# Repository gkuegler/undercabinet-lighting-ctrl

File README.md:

<!-- | Supported Targets | ESP32 | ESP32-C2 | ESP32-C3 | ESP32-C6 | ESP32-H2 | ESP32-P4 | ESP32-S2 | ESP32-S3 | -->
<!-- | ----------------- | ----- | -------- | -------- | -------- | -------- | -------- | -------- | -------- | -->
| Supported Targets: | ESP32 | ESP32-S3 |
| ------------ | --- | --- |

Uses ESP-IDF v5.2

# Kitchen Under Cabinet Lighting Controller
This controller mounts upside down underneath kitchen cabinets enables the undercabinet lighting to be turned on/off with with wave of a hand.
This is the source code for a gesture activated lighting controller which utilizes a HC-SR04 ultrasonic distance sensor.

This controller is designed to be mounted upside down underneath kitchen cabinets. It's compatible with 12-24VDC LEDs.

# 3D Printed Case
The custom case was designed in OnShape. See the link below for the project file.
https://cad.onshape.com/documents/ef51b7b650ada663375a7fe6/w/94d192bce853b8bb4785d228/e/2ec3751c0459ca22265b7e29

## Folder contents

ESP-IDF projects are built using CMake. 

Below is short explanation of remaining files in the project folder.
```
├── CMakeLists.txt
├── components (project libraries, see ESP-IDF for info on components)
├── kicad (project files for custom PCB)
├── main
│   ├── CMakeLists.txt
│   └── main.cpp (entry point)
└── README.md
```

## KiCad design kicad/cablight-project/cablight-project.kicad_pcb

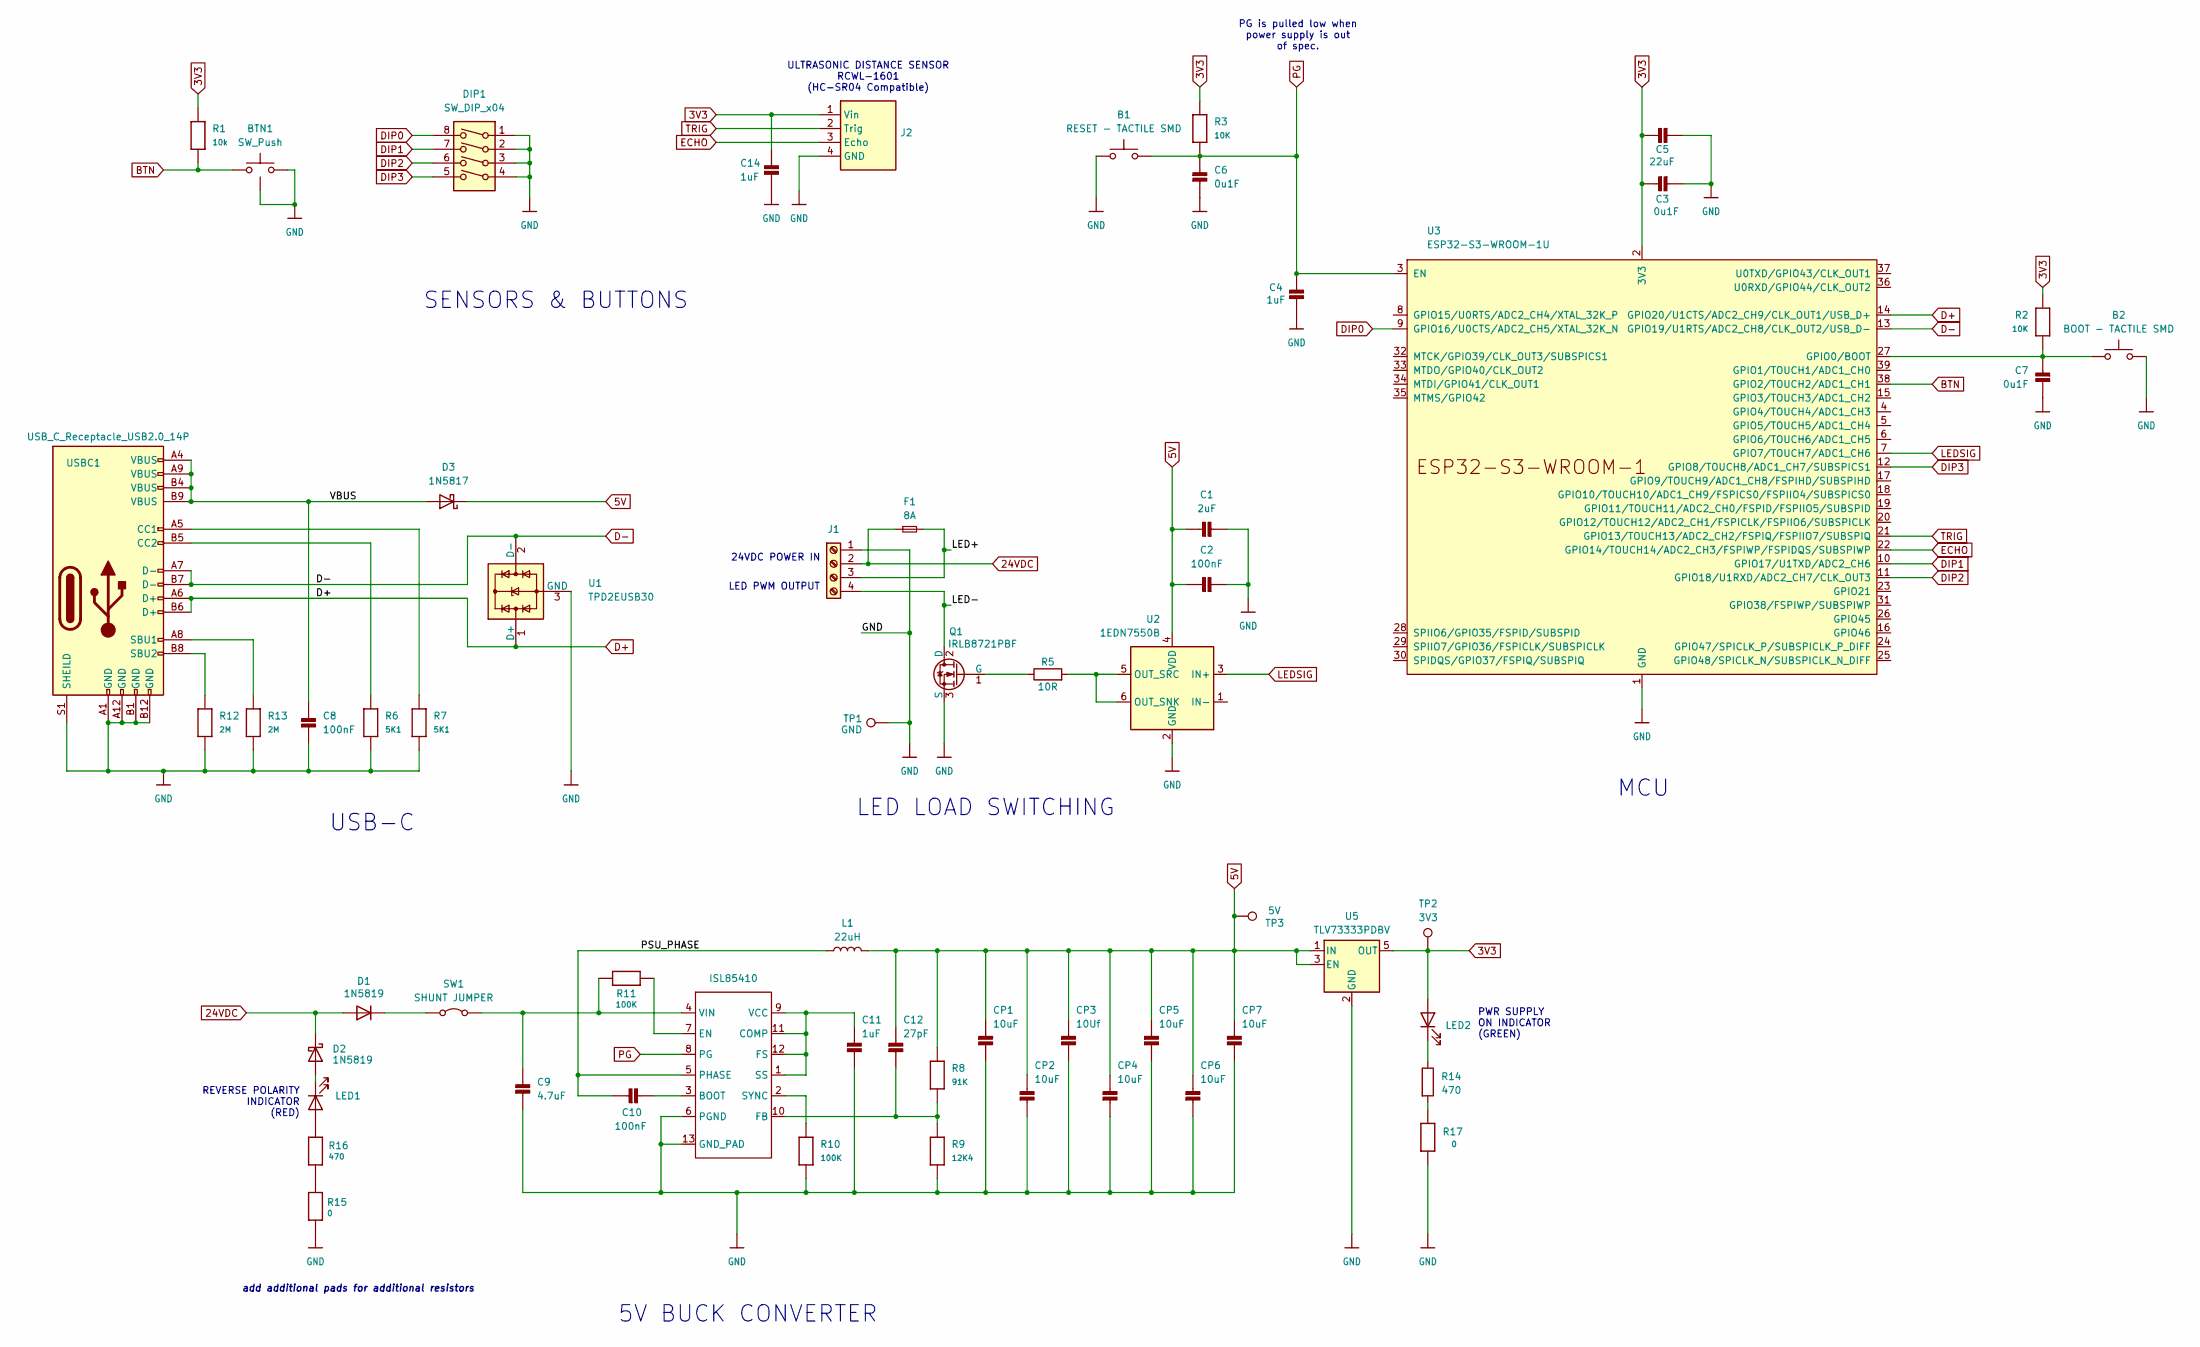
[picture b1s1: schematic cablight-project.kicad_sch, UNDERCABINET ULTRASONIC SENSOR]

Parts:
B1: RESET - TACTILE SMD; tactile Eswitch TL3365
B2: BOOT - TACTILE SMD; tactile Eswitch TL3365
BTN1: SW_Push; Tactile Switch Wurth
C1: 2uF; C_0805_2012Metric_Pad1.18x1.45mm_HandSolder
C2, C8, C10: 100nF; C_0805_2012Metric_Pad1.18x1.45mm_HandSolder
C3, C6, C7: 0u1F; C_0805_2012Metric_Pad1.18x1.45mm_HandSolder
C4, C11, C14: 1uF; C_0805_2012Metric_Pad1.18x1.45mm_HandSolder
C5: 22uF; C_0805_2012Metric_Pad1.18x1.45mm_HandSolder
C9: 4.7uF; C_0805_2012Metric_Pad1.18x1.45mm_HandSolder
C12: 27pF; C_0805_2012Metric_Pad1.18x1.45mm_HandSolder
CP1, CP2, CP4, CP5, CP6, CP7: 10uF; C_0805_2012Metric_Pad1.18x1.45mm_HandSolder
CP3: 10Uf; C_0805_2012Metric_Pad1.18x1.45mm_HandSolder
D1, D2: 1N5819; D_DO-41_SOD81_P2.54mm_Vertical_KathodeUp
D3: 1N5817; D_DO-41_SOD81_P2.54mm_Vertical_KathodeUp
DIP1: SW_DIP_x04; DIP-4 DS04-254 SAME SKY
F1: 8A; Fuse_1206_3216Metric_Pad1.42x1.75mm_HandSolder
J1: Screw_Term_1x4_5mm; Molex 4pin Terminal Block
J2: RCWL-1601; Terminal Block 4-Pin 2mm Pitch
L1: 22uH; Wurth Inductor 22uH 1.15A 225mOhm
LED1, LED2: LED 0603; LED_0603_1608Metric_Pad1.05x0.95mm_HandSolder
Q1: IRLB8721PBF; TO-220F-3_H_Heatsink
R1: 10k; R_0805_2012Metric_Pad1.20x1.40mm_HandSolder
R2, R3: 10K; R_0805_2012Metric_Pad1.20x1.40mm_HandSolder
R5: 10R; R_0805_2012Metric_Pad1.20x1.40mm_HandSolder
R6, R7: 5K1; R_0805_2012Metric_Pad1.20x1.40mm_HandSolder
R8: 91K; R_0805_2012Metric_Pad1.20x1.40mm_HandSolder
R9: 12K4; R_0805_2012Metric_Pad1.20x1.40mm_HandSolder
R10, R11: 100K; R_0805_2012Metric_Pad1.20x1.40mm_HandSolder
R12, R13: 2M; R_0805_2012Metric_Pad1.20x1.40mm_HandSolder
R14, R16: 470; R_0805_2012Metric_Pad1.20x1.40mm_HandSolder
R15, R17: 0; R_0805_2012Metric_Pad1.20x1.40mm_HandSolder
SW1: SHUNT JUMPER; 1x02_P2.54mm_Vertical_Shunt
T1: ISL85410
TP1: GND; TestPoint_THTPad_D1.0mm_Drill0.5mm
TP2: 3V3; TestPoint_THTPad_D1.0mm_Drill0.5mm
TP3: 5V; TestPoint_THTPad_D1.0mm_Drill0.5mm
U1: TPD2EUSB30; DRT3
U2: 1EDN7550B; SOT-23-6
U3: ESP32-S3-WROOM-1U
U5: TLV73333PDBV; SOT-23-5
USBC1: USB_C_Receptacle_USB2.0_14P; usbc-GCT_USB4160-03-0170-C_REVA2

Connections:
3V3: C3.1, C5.1, C14.1, J2.1 (Vin), LED2.2 (A), R1.2, R2.2, R3.2, TP2.1, U3.2 (3V3), U5.5 (OUT)
5V: C1.1, C2.1, C12.1, CP1.1, CP2.1, CP3.1, CP4.1, CP5.1, CP6.1, CP7.1, D3.1 (K), L1.2, R8.2, TP3.1, U2.4 (VDD), U5.1 (IN), U5.3 (EN)
24VDC: D1.2 (A), D2.1 (K), F1.1, J1.2
/LED+: F1.2, J1.3
/LED-: J1.4, Q1.2 (D)
/PSU_PHASE: C10.1, L1.1, T1.5 (PHASE)
/VBUS: C8.1, D3.2 (A), USBC1.A4 (VBUS), USBC1.A9 (VBUS), USBC1.B4 (VBUS), USBC1.B9 (VBUS)
BTN: BTN1.1, R1.1, U3.38 (GPIO2/TOUCH2/ADC1_CH1)
D+: U1.1 (D+), U3.14 (GPIO20/U1CTS/ADC2_CH9/CLK_OUT1/USB_D+), USBC1.A6 (D+), USBC1.B6 (D+)
D-: U1.2 (D-), U3.13 (GPIO19/U1RTS/ADC2_CH8/CLK_OUT2/USB_D-), USBC1.A7 (D-), USBC1.B7 (D-)
DIP0: DIP1.8, U3.9 (GPIO16/U0CTS/ADC2_CH5/XTAL_32K_N)
DIP1: DIP1.7, U3.10 (GPIO17/U1TXD/ADC2_CH6)
DIP2: DIP1.6, U3.11 (GPIO18/U1RXD/ADC2_CH7/CLK_OUT3)
DIP3: DIP1.5, U3.12 (GPIO8/TOUCH8/ADC1_CH7/SUBSPICS1)
ECHO: J2.3 (Echo), U3.22 (GPIO14/TOUCH14/ADC2_CH3/FSPIWP/FSPIDQS/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)
GND: B1.1, B2.1, BTN1.2, BTN1.GND, C1.2, C2.2, C3.2, C4.2, C5.2, C6.2, C7.2, C8.2, C9.2, C11.2, C14.2, CP1.2, CP2.2, CP3.2, CP4.2, CP5.2, CP6.2, CP7.2, DIP1.1, DIP1.2, DIP1.3, DIP1.4, J1.1, J2.4 (GND), Q1.3 (S), R6.2, R7.2, R9.1, R10.1, R12.2, R13.2, R15.2, R17.2, T1.6 (PGND), T1.13 (GND_PAD), TP1.1, U1.3 (GND), U2.2 (GND), U3.1 (GND), U3.40 (GND), U3.41 (GND), U5.2 (GND), USBC1.A1 (GND), USBC1.A12 (GND), USBC1.B1 (GND), USBC1.B12 (GND), USBC1.S1 (SHEILD)
LEDSIG: U2.3 (IN+), U3.7 (GPIO7/TOUCH7/ADC1_CH6)
unnamed: D1.1 (K), SW1.1 (A)
unnamed: D2.2 (A), LED1.1 (K)
unnamed: LED1.2 (A), R16.1
unnamed: LED2.1 (K), R14.1
unnamed: Q1.1 (G), R5.2
unnamed: R14.2, R17.1
unnamed: R15.1, R16.2
unnamed: C9.1, R11.2, SW1.2 (B), T1.4 (VIN)
unnamed: C10.2, T1.3 (BOOT)
unnamed: C11.1, T1.1 (SS), T1.9 (VCC), T1.11 (COMP), T1.12 (FS)
unnamed: R11.1, T1.7 (EN)
unnamed: C12.2, R8.1, R9.2, T1.10 (FB)
unnamed: R10.2, T1.2 (SYNC)
unnamed: R5.1, U2.5 (OUT_SRC), U2.6 (OUT_SNK)
unnamed: B2.2, C7.1, R2.1, U3.27 (GPIO0/BOOT)
unnamed: R7.1, USBC1.A5 (CC1)
unnamed: R6.1, USBC1.B5 (CC2)
unnamed: R13.1, USBC1.A8 (SBU1)
unnamed: R12.1, USBC1.B8 (SBU2)
PG: B1.2, C4.1, C6.1, R3.1, T1.8 (PG), U3.3 (EN)
TRIG: J2.2 (Trig), U3.21 (GPIO13/TOUCH13/ADC2_CH2/FSPIQ/FSPIIO7/S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)

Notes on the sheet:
add additional pads for additional resistors
REVERSE POLARITY INDICATOR (RED)
5V BUCK CONVERTER
LED LOAD SWITCHING
PG is pulled low when power supply is out of spec.
USB-C
24VDC POWER IN
MCU
LED PWM OUTPUT
SENSORS & BUTTONS
ULTRASONIC DISTANCE SENSOR RCWL-1601 (HC-SR04 Compatible)
PWR SUPPLY ON INDICATOR (GREEN)

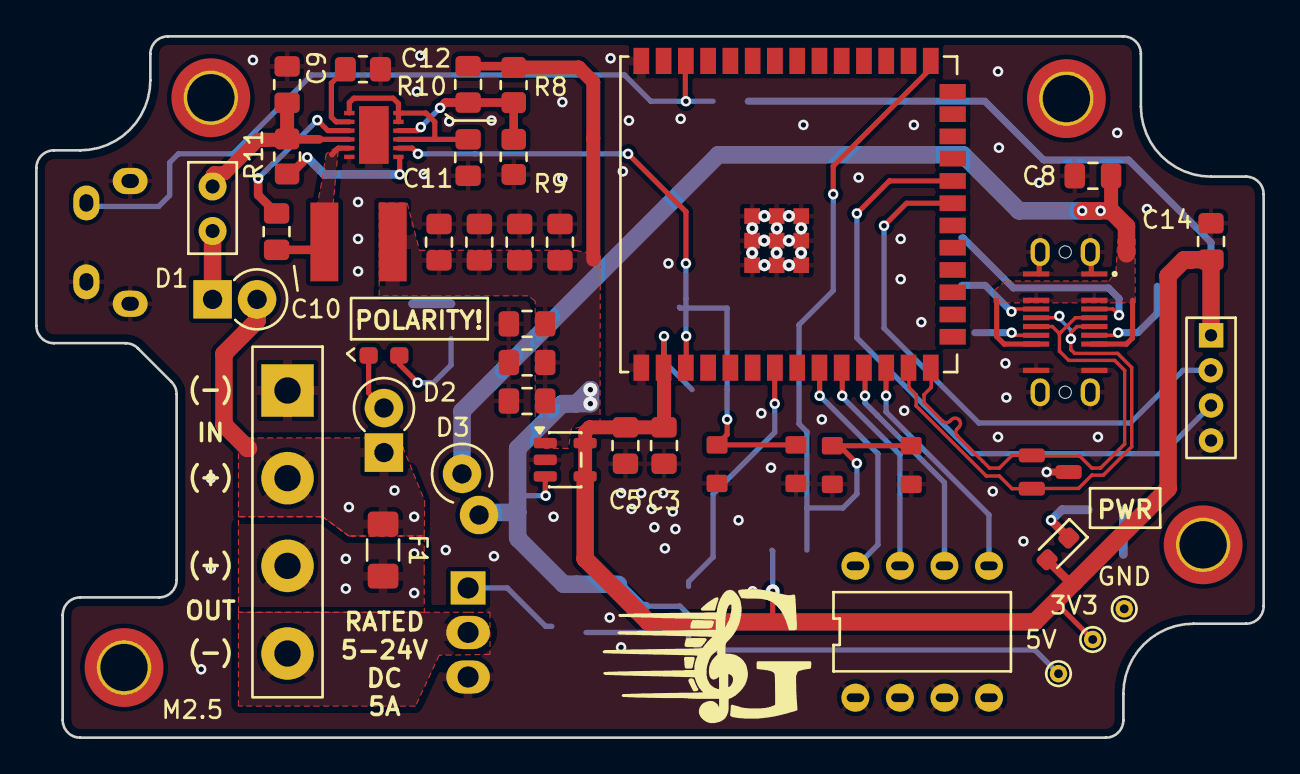
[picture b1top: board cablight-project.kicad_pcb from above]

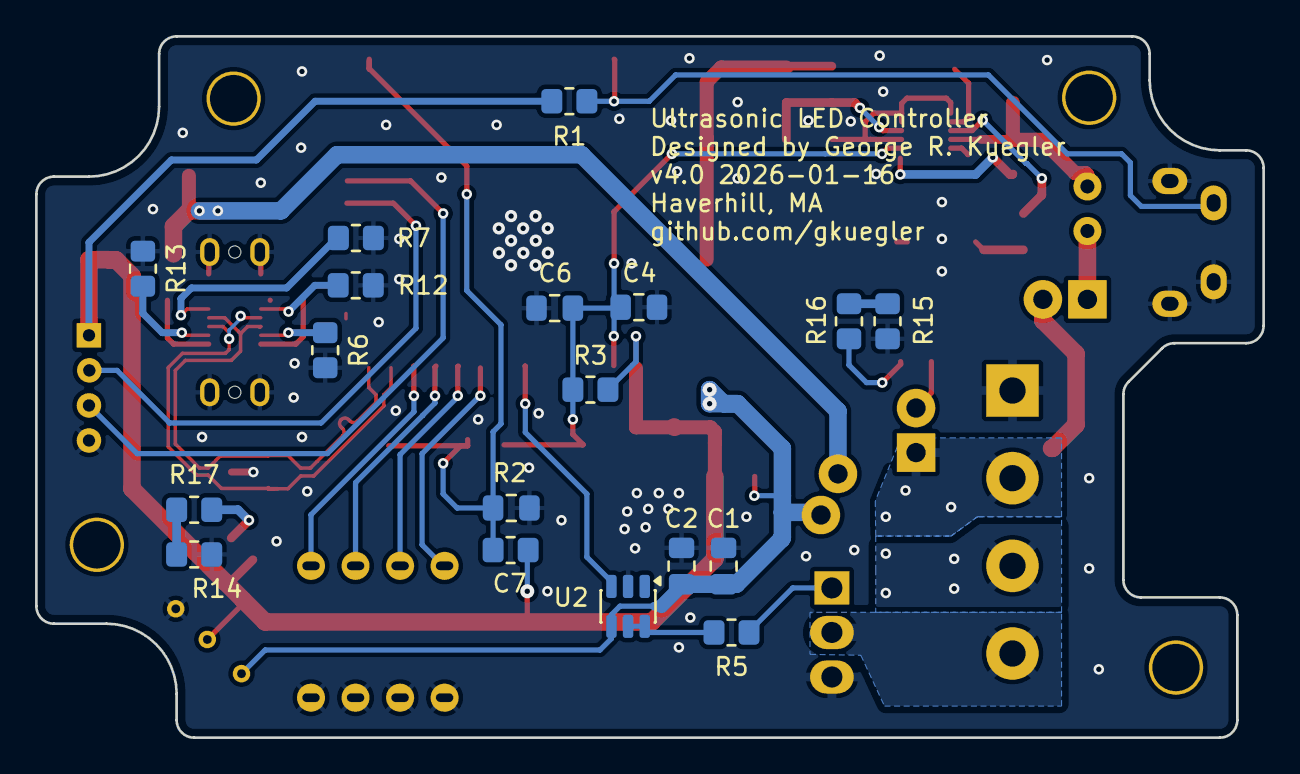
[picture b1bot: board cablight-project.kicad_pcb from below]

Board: 4 copper layers, 70.0 x 40.0 mm, 65 parts (18 on the bottom side), 38 nets.

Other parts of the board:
M2.5, M2.5#2, M2.5#3, M2.5#4: MountingHole_2.7mm_M2.5_ISO7380_Pad_TopOnly
S1: RCWL-1601-outline; RCWL-1601-Outline

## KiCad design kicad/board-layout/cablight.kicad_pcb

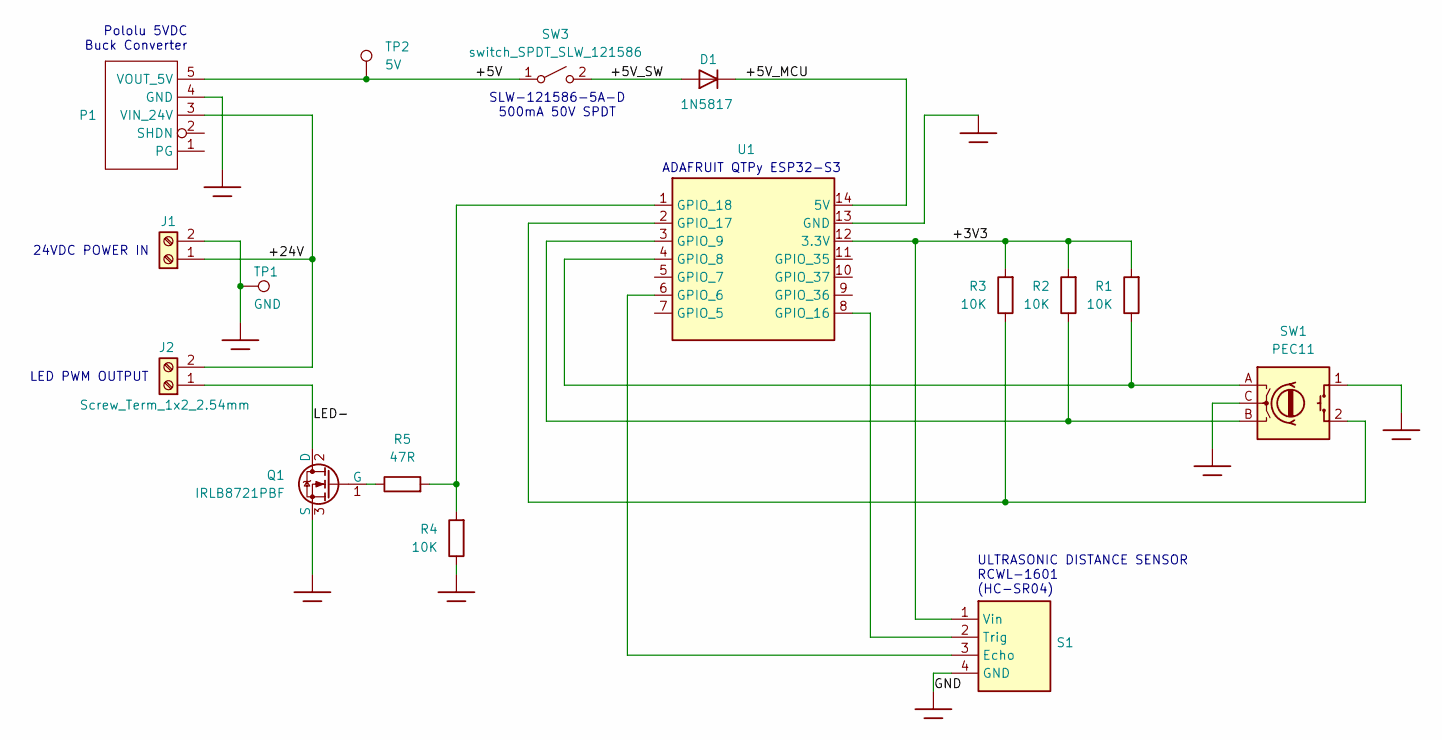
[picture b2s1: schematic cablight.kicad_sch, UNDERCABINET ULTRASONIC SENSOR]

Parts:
D1: 1N5817; D_DO-41_SOD81_P2.54mm_Vertical_KathodeUp
J1, J2: Screw_Term_1x2_2.54mm; 2xTermBlock_254mm
P1: Pololu D24V10F5; Pololu_5V_H
Q1: IRLB8721PBF; TO-220F-3_H_Heatsink
R1, R2, R3, R4: 10K; R_Axial_DIN0207_L6.3mm_D2.5mm_P10.16mm_Horizontal
R5: 47R; R_Axial_DIN0207_L6.3mm_D2.5mm_P10.16mm_Horizontal
S1: RCWL-1601
SW1: PEC11; Bourns-PEC11R
SW3: switch_SPDT_SLW_121586; CUI_SPDT_500mA_3mm
TP1: GND; TestPoint_Plated_Hole_D2.0mm
TP2: 5V; TestPoint_Plated_Hole_D2.0mm
U1: AdafruitQTPyEsp32S3

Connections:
/+3V3: R1.1, R2.1, R3.1, S1.1 (Vin), U1.12 (3.3V)
/+5V: P1.5 (VOUT_5V), SW3.1, TP2.1
/+5V_MCU: D1.1 (K), U1.14 (5V)
/+5V_SW: D1.2 (A), SW3.2
/+24V: J1.1, J2.2, P1.3 (VIN_24V)
/LED-: J2.1, Q1.2 (D)
<NO NET>: J1.2, P1.4 (GND), Q1.3 (S), R4.2, S1.4 (GND), SW1.1 (S1), SW1.C, TP1.1, U1.13 (GND)
unnamed: Q1.1 (G), R5.2
unnamed: S1.3 (Echo), U1.6 (GPIO_6)
unnamed: S1.2 (Trig), U1.8 (GPIO_16)
unnamed: R3.2, SW1.2 (S2), U1.2 (GPIO_17)
unnamed: R1.2, SW1.A, U1.4 (GPIO_8)
unnamed: R2.2, SW1.B, U1.3 (GPIO_9)
unnamed: R4.1, R5.1, U1.1 (GPIO_18)

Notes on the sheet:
ULTRASONIC DISTANCE SENSOR RCWL-1601 (HC-SR04)
Pololu 5VDC Buck Converter
SLW-121586-5A-D 500mA 50V SPDT
24VDC POWER IN
LED PWM OUTPUT
ADAFRUIT QTPy ESP32-S3

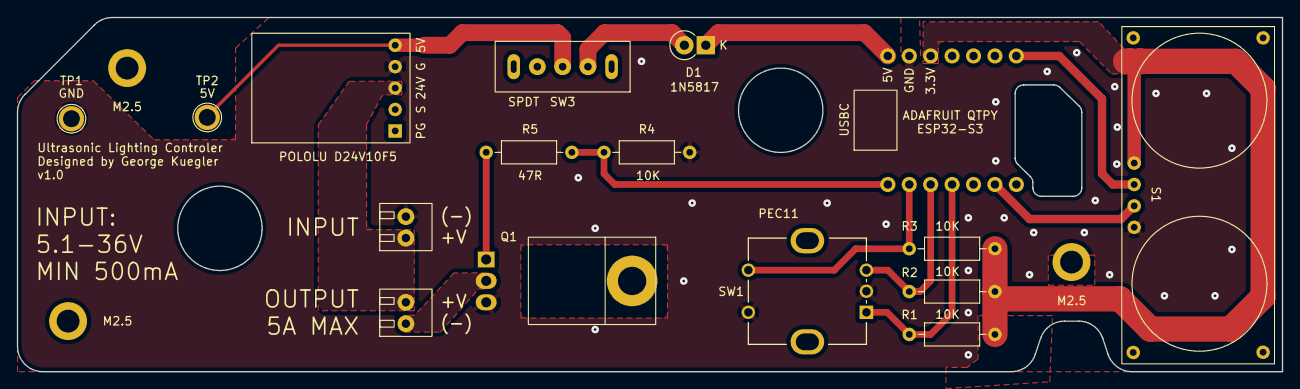
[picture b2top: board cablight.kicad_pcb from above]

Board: 2 copper layers, 150.0 x 42.0 mm, 17 parts (1 on the bottom side), 14 nets.

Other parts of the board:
M3: MountingHole_3.2mm_M3_ISO14580_Pad_TopOnly

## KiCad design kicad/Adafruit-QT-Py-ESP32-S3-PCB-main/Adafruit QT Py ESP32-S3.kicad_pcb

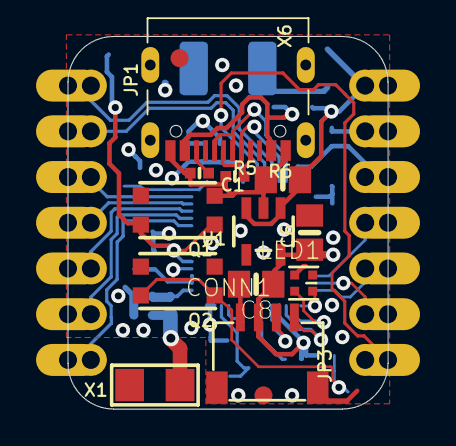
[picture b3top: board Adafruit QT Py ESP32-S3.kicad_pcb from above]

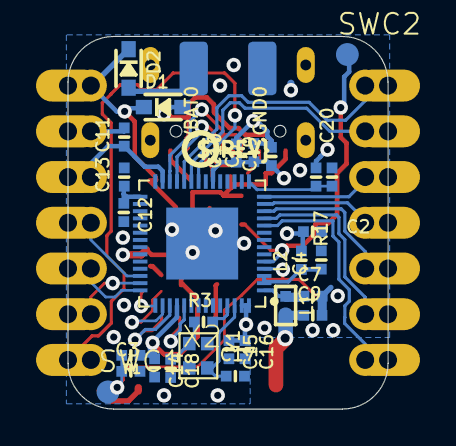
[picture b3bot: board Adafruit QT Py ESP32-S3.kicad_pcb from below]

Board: 4 copper layers, 17.8 x 20.7 mm, 49 parts (32 on the bottom side), 34 nets.

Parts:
C1, C6, C8: 22uF; 0805-NO
C2, C3, C5, C13, C15, C19, C20: 1uF; _0402NO
C4, C10, C11, C12, C14, C16: 0.1uF; _0402NO
C7, C9: TBD; _0402NO
C17, C18: 16pF; _0402NO
CONN1: STEMMA_I2C_QTSKINNY; JST_SH4_SKINNY
D1, D2: NSR0320; SOD-323_MINI
GND0: TESTPOINT_MINUS_1X3MM
JP1, JP3: 1X07_CASTEL
L1: 2nH; _0402NO
L2: 0 ohm; _0402
LED1: WS2812B_SK6805_1515; SK6805_1515
Q1: BOOT0; BTN_KMR2_4.6X2.8
Q2: reset; BTN_KMR2_4.6X2.8
R1: 10K; _0402NO
R3: 0; _0402NO
R5, R6: 5.1K; _0402NO
R17: 1Meg; _0402NO
SWC1, SWC2: TPB1,27; B1,27_385
U1: AP2112K-3.3; SOT23-5
U$6, U$8: FIDUCIAL_1MM
U$7: QTPY_ESP32_TOP
U$11: QTPYS3_BOT
U$12: PCBFEAT-REV-040
VBAT0: TESTPOINT_PLUS_1X3MM
X1: 2.4 GHz Antenna; ANT_2450AT18B100
X2: ESP32-S3QFN54; QFN56_7X7
X6: USB TYPE C; USB_C_CUSB31-CFM2AX-01-X
Y1: 40MHz; CRYSTAL_2X1.6

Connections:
3.3V: C2.1, C5.1, C6.1, C8.1, C10.1, C11.1, C14.1, C15.1, C16.1, C19.1, CONN1.2, JP3.5, JP3.5C, L1.1, R1.1, U1.5, X2.20, X2.27, X2.46, X2.55, X2.56
+5V: C1.1, D1.C, D2.C, JP3.7, JP3.7C, U1.1, U1.3
A0: JP1.1, JP1.1C, X2.24
A1: JP1.2, JP1.2C, X2.23
A2: JP1.3, JP1.3C, X2.14
A3: JP1.4, JP1.4C, X2.13
CC1: R6.2, X6.A5
CC2: R5.2, X6.B5
D+: X2.26, X6.A6, X6.B6
D-: X2.25, X6.A7, X6.B7
GND: C1.2, C2.2, C3.2, C4.2, C5.2, C6.2, C7.2, C8.2, C9.2, C10.2, C11.2, C12.2, C13.2, C14.2, C15.2, C16.2, C17.2, C18.2, C19.2, C20.2, CONN1.1, CONN1.MT1, CONN1.MT2, GND0.P$1, JP3.6, JP3.6C, LED1.4, Q1.B, Q1.B', Q2.B, Q2.B', R5.1, R6.1, R17.1, U1.2, X2.57, X6.A1B12, X6.B1A12
IO0: Q1.A, Q1.A', SWC2.TP, X2.5
IO10_DBLTAP: C20.1, R17.2, X2.15
MISO: JP3.3, JP3.3C, X2.42
MOSI: JP3.4, JP3.4C, X2.40
unnamed: R3.2, X2.53
unnamed: C7.1, L2.2, X2.1
unnamed: C9.1, L2.1, X1.FP
unnamed: C17.1, X2.54, Y1.3
unnamed: C18.1, R3.1, Y1.1
NEOPIX: LED1.1, X2.44
NEOPIX_PWR: LED1.2, X2.43
RX: JP3.1, JP3.1C, X2.22
SCK: JP3.2, JP3.2C, X2.41
SCL: JP1.6, JP1.6C, X2.11
SCL1: CONN1.4, X2.45
SDA: JP1.5, JP1.5C, X2.12
SDA1: CONN1.3, X2.47
TX: JP1.7, JP1.7C, X2.10
VBAT: D2.A, VBAT0.P$1
VBUS: D1.A, X6.A4B9, X6.B4A9
VDD3P3: C4.1, L1.2, X2.2, X2.3
VDD_SPI: C12.1, C13.1, X2.29
~RESET: C3.1, Q2.A, Q2.A', R1.2, SWC1.TP, X2.4

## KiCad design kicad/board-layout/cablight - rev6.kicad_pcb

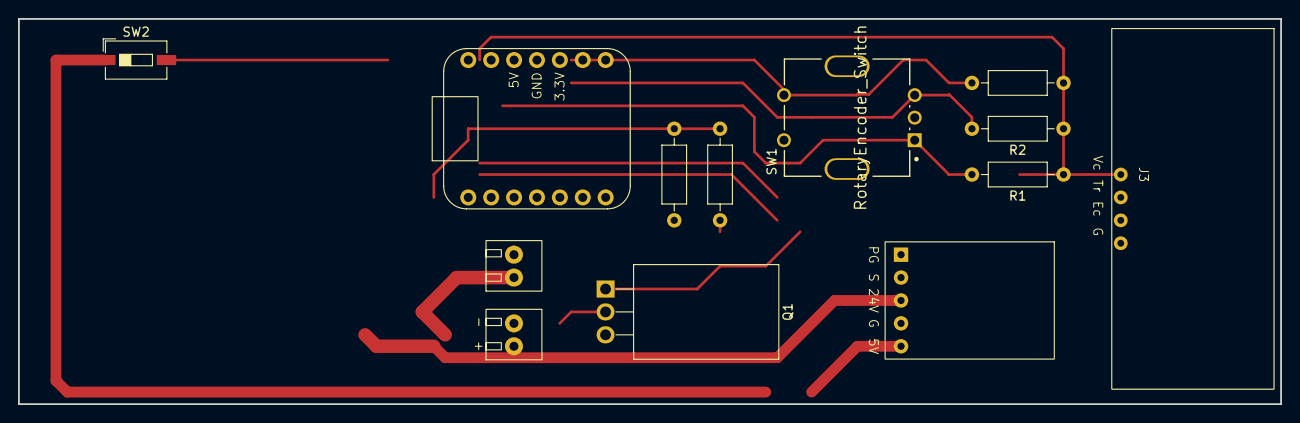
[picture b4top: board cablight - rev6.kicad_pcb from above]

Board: 2 copper layers, 140.0 x 42.7 mm, 13 parts (0 on the bottom side), 12 nets.

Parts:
J1, J2: Screw_Terminal_01x02; 2xTermBlock_254mm
J3: Screw_Terminal_HCSR04; RCWL-1601
Pololu_5V_1: Pololu_5V_H
Q1: IRLB8721PBF; TO-220F-3_H_Heatsink
R1, R2, R3, R4: 10K; R_Axial_DIN0207_L6.3mm_D2.5mm_P10.16mm_Horizontal
R5: 47; R_Axial_DIN0207_L6.3mm_D2.5mm_P10.16mm_Horizontal
SW1: RotaryEncoder_Switch; Bourns-PEC11R-4220F-S0024-0-0-0
SW2: SW_SPST; SW_DIP_SPSTx01_Slide_6.7x4.1mm_W6.73mm_P2.54mm_LowProfile_J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
U1: AdafruitQTPyEsp32S3

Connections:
/+24V: J1.1, J2.1, Pololu_5V_1.3 (VIN_24V)
<NO NET>: J1.2, J3.4 (GND), Pololu_5V_1.4 (GND), Q1.3 (S), R4.2, SW1.1 (S1), SW1.C, U1.13 (GND)
unnamed: J2.2, Q1.2 (D)
unnamed: J3.3 (ECHO), U1.7 (GPIO_5)
unnamed: J3.1 (Vcc), R1.1, R2.1, R3.1, U1.12 (3.3V)
unnamed: Pololu_5V_1.5 (VOUT_5V), SW2.1 (A)
unnamed: Q1.1 (G), R5.2
unnamed: R3.2, SW1.2 (S2), U1.8 (GPIO_16)
unnamed: SW2.2 (B), U1.14 (5V)
unnamed: R1.2, SW1.A, U1.5 (GPIO_7)
unnamed: R2.2, SW1.B, U1.3 (GPIO_9)
unnamed: R4.1, R5.1, U1.1 (GPIO_18)

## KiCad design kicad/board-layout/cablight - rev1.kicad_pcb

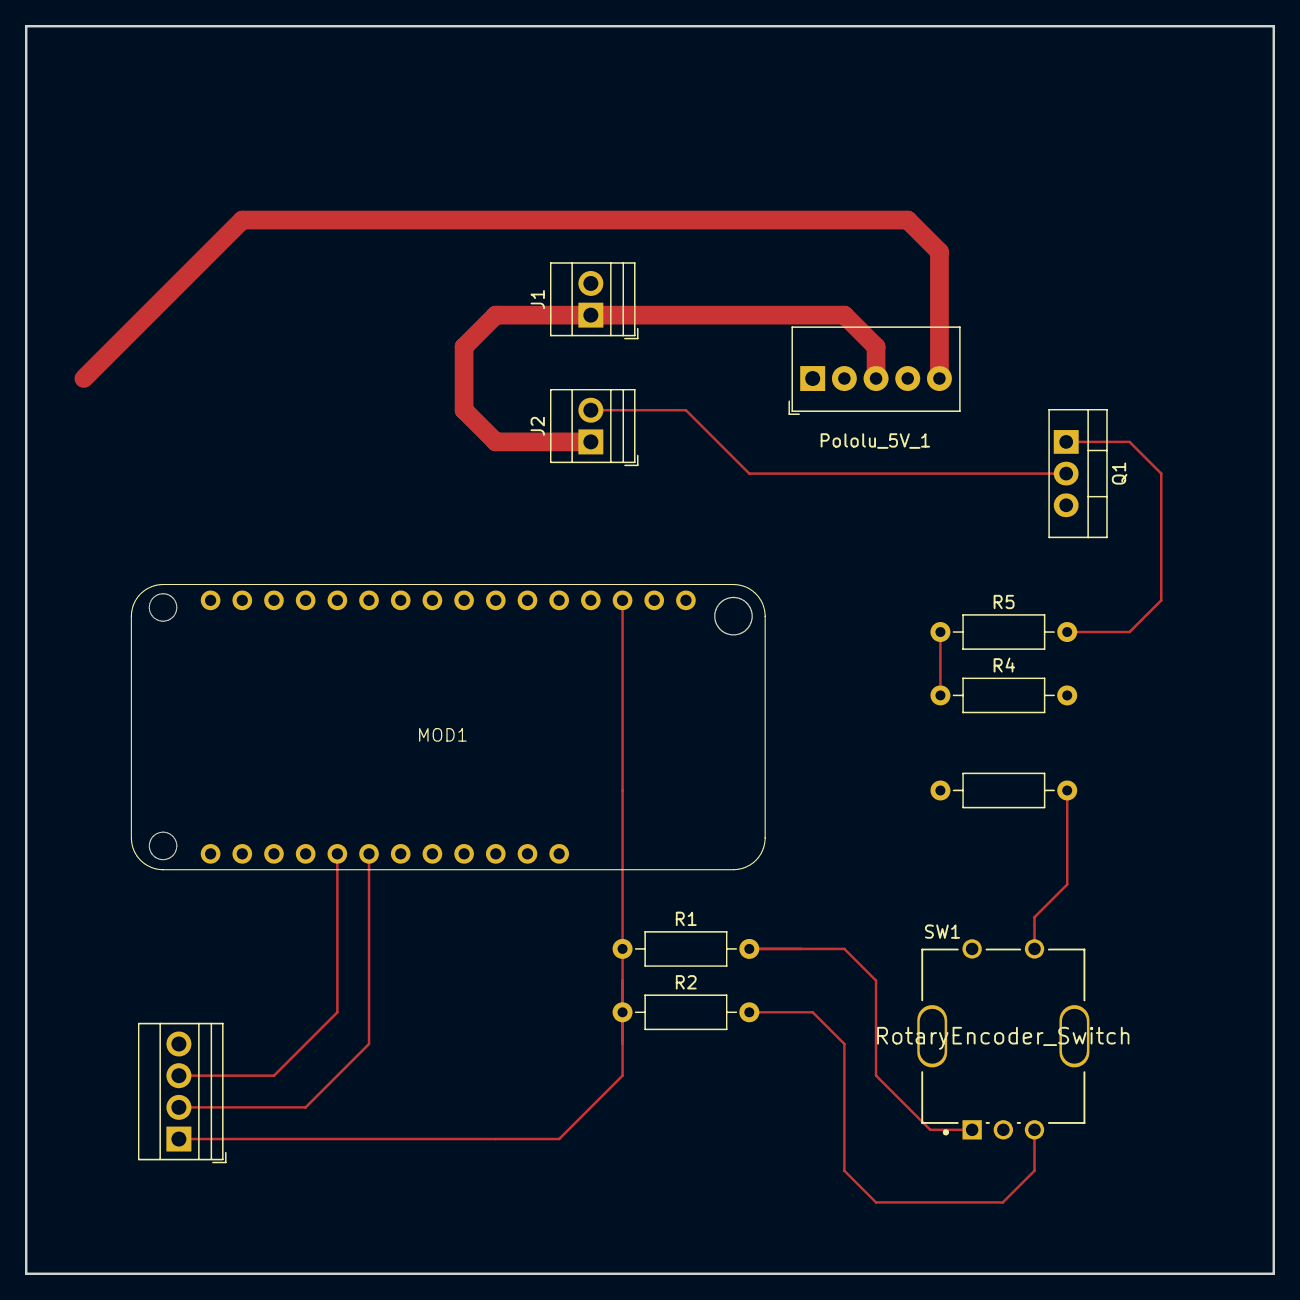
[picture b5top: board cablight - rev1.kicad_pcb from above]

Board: 2 copper layers, 100.0 x 100.0 mm, 12 parts (0 on the bottom side), 13 nets.

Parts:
J1, J2: Screw_Terminal_01x02; TerminalBlock_Xinya_XY308-2.54-2P_1x02_P2.54mm_Horizontal
J3: Screw_Terminal_HCSR04; TerminalBlock_Xinya_XY308-2.54-4P_1x04_P2.54mm_Horizontal
MOD1: ADAFRUIT_FEATHER_TFT_ESP32_S3; AdafruitFeatherTFTEsp32S3
Pololu_5V_1: Pololu5PinThroughHole
Q1: IRLB8721PBF; TO-220-3_Vertical
R1, R2, R3, R4: 10K; R_Axial_DIN0207_L6.3mm_D2.5mm_P10.16mm_Horizontal
R5: 47; R_Axial_DIN0207_L6.3mm_D2.5mm_P10.16mm_Horizontal
SW1: RotaryEncoder_Switch; Bourns-PEC11R-4220F-S0024-0-0-0

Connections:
/+24V: J1.1, J2.1, Pololu_5V_1.3 (VIN_24V)
<NO NET>: J1.2, J3.4 (GND), MOD1.4 (GND), Pololu_5V_1.4 (GND), Q1.3 (S), R4.2, SW1.1 (S1), SW1.C
unnamed: J2.2, Q1.2 (D)
unnamed: J3.3 (ECHO), MOD1.21 (GPIO9_D9)
unnamed: J3.2 (TRIG), MOD1.22 (GPIO10_D10)
unnamed: J3.1 (Vcc), MOD1.3 (3.3V), R1.1, R2.1, R3.1
unnamed: MOD1.27 (EN), Pololu_5V_1.1 (PG)
unnamed: MOD1.14 (GPIO2_RX), R4.1, R5.1
unnamed: MOD1.9 (GPIO14_A4), R3.2, SW1.2 (S2)
unnamed: MOD1.7 (GPIO16_A2), R2.2, SW1.B
unnamed: MOD1.5 (GPIO18_A0), R1.2, SW1.A
unnamed: MOD1.26 (V_USB), Pololu_5V_1.5 (VOUT_5V)
unnamed: Q1.1 (G), R5.2

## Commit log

2024-08-29 initial commit - working HC-SR04, LVGL, Rotary Encoder, and Button
2024-09-02 working LEDC basic driver
2024-09-02 make led dimmable from rotary encoder input
2024-09-02 Implement watchdog timeout on ranging session.
2024-09-02 add timmout dimmer to ledc
2024-09-02 remove .vscode files from index
2024-09-02 move disp pdf to spi library
2024-09-10 create board layout in kicad
2024-09-21 update board layout
2024-09-22 pcb board review
2024-09-30 board updates
2024-09-30 restructure folders
2024-10-17 archive kiCAD project
2024-10-17 remove gui
2024-10-17 conver event queue to class
2024-11-06 remove eventq and fix warnings
2024-11-06 ignore kicad backups
2024-11-06 cleanup naming
2024-11-06 remove extraneous library files
2024-11-06 adjust timeout and convert to ticks in classes
2024-11-12 update comments/documentation
2024-11-12 add enable flag for led timeout & warning
2024-11-12 cleanup
2025-03-29 format with clang
2025-03-29 update docs & comments
2025-09-15 Add Button code support and make ultrasonic notify from task.
2025-09-15 change inital thresh dist
2025-09-15 update todo's and plans
2025-09-15 code cleanup for v1.3
2025-09-16 create esp & freertos error check functions
2025-09-16 put gpio init in button init func
2025-09-19 add DIP switch to kicad
2025-09-19 flip Q1 and rotate
2025-09-20 add right angle switch cutsheet
2025-09-20 not working progress
2025-09-22 improvments
2025-09-24 progress
2025-09-24 final v1
2025-09-26 pre release board layout
2025-09-26 fix bug
2025-10-01 Layout KiCAD for DIP switches and button.
2025-10-06 submit board v2
2025-10-06 remove 4th dip switch
2025-11-11 add datasheets
2025-11-11 add kicad to gitignore
2025-11-20 schematic USB-C, LDO, and MCU with rst + boot btns
2025-11-20 select footprints. layout buck 5v converter
2025-11-24 add design docs
2025-11-24 bad schematic checkpoint
2025-11-25 fixed missing symbols
2025-11-25 80 percent layout v1
2025-11-25 drc checks
2025-11-26 99 percent layout v1
2025-11-26 change fuse pkg & add datasheets
2025-12-01 plot fab for final check
2025-12-02 create more space for usb esd
2025-12-03 schematic cleanup
2025-12-03 further board changes
2025-12-12 remove unused parts
2026-01-17 add gate driver and linear regulator
2026-01-18 align button to correct location
2026-01-19 generate prelim output for gerbers
2026-01-19 jlpcb order
2026-03-15 add Seeed studio esp32s2 board support
